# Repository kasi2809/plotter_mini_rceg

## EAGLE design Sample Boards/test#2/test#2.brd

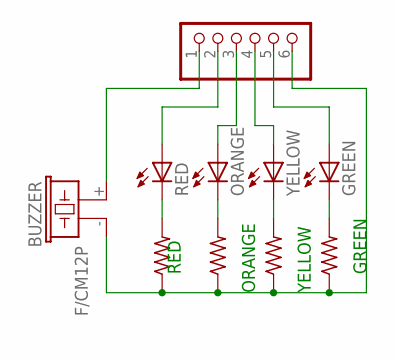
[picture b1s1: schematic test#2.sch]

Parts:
BUZZER: F/CM12P
GND: PINHD-1X6; 1X06
GREEN: LED5MM
ORANGE: LED5MM
R1, R2, R3, R4: R-US_0204/7; 0204/7
RED: LED5MM
YELLOW: LED5MM

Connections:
unnamed: R1.2, RED.K (C)
unnamed: ORANGE.K (C), R2.2
unnamed: R3.2, YELLOW.K (C)
unnamed: GREEN.K (C), R4.2
unnamed: BUZZER.+ (1), GND.1
unnamed: GND.2, RED.A
unnamed: GND.3, ORANGE.A
unnamed: GND.4, YELLOW.A
unnamed: GND.5, GREEN.A
unnamed: BUZZER.- (2), GND.6, R1.1, R2.1, R3.1, R4.1

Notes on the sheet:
RED
ORANGE
YELLOW
GREEN

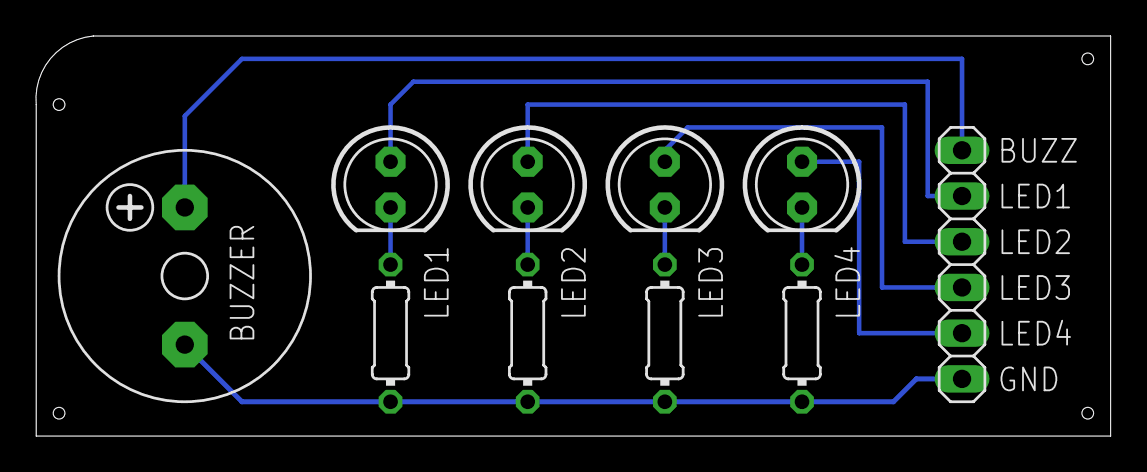
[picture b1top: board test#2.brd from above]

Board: 2 copper layers, 59.7 x 22.2 mm, 10 parts (0 on the bottom side), 10 nets.

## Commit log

2020-12-18 python test file
2020-12-18 image added
2020-12-18 cnc pcb
2020-12-19 points sorted
2020-12-19 python and ardiuno
2020-12-19 Add files via upload
    arduino file
2020-12-19 code pathi ready
2020-12-19 code paathi ready
2020-12-20 final done
2020-12-26 Create planes.py
    planes.py is working fine
2020-12-26 zombie
2020-12-26 Update ch2.py
    vv
2020-12-26 Update ch2.py
    vv
2020-12-27 round 2
2020-12-27 Update opencv_round2.py
    Code Cleaned
2020-12-27 Update opencv_round2.py
    Code nettoyé!
2020-12-27 Update opencv_round2.py
    Code terminé
2021-01-01 added first 2 slides
2021-01-01 check last line
2021-01-02 power point slides updated
2021-01-04 removed block diagram contents in list form
2021-01-04 removed the slide that block diagram contents in list form
2021-01-04 back, in worst case scenario
2021-01-04 Checkout cnc_pcb_backup.py for fixing your problem, Kasi
2021-01-05 small change
2021-01-05 backup changed
2021-01-05 ppt changed
2021-01-05 update test#3
2021-01-06 CHANGED
2021-01-06 ppt done with working video
2021-01-08 ppt done
2021-01-11 final ppt
2021-01-13 update 3d files
2021-01-13 Revert "Merge branch 'main' of https://github.com/kasi2809/plotter_mini_rceg into main"
    This reverts commit 7577533d4386926605863180dde8e38fc6772f04, reversing
    changes made to a27e460bd5644b4b11c77f6051598fdd9a1d0213.
2021-01-18 added C code for MSP430
    I haven't checked if this code properly functions. This version of code
    requires a minor change in the Python program running in PC
2021-01-18 imported entire CCS project
2021-02-17 Revert "Revert "Merge branch 'main' of https://github.com/kasi2809/plotter_mini_rceg into main""
    This reverts commit be6ef2e4d0919a5fc9b937987a180cd1cd016e2f.
2021-03-22 chnaged
2021-05-07 video_added
2021-05-14 added extruder tester
